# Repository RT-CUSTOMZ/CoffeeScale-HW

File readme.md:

# HX711 Board

* RATE Pin connected to GND -> 10 Hz mode
* X1 Pin connected to GND -> on-chip oscillator is activate

## InteractiveHtmlBom

[Link to interactive bom](https://htmlpreview.github.io/?https://raw.githubusercontent.com/RT-CUSTOMZ/CoffeeScale-HW/master/bom/ibom.html)

## Schematics

[Link to Schematic pdf](./coffee-scale.pdf )

## Messbrücke

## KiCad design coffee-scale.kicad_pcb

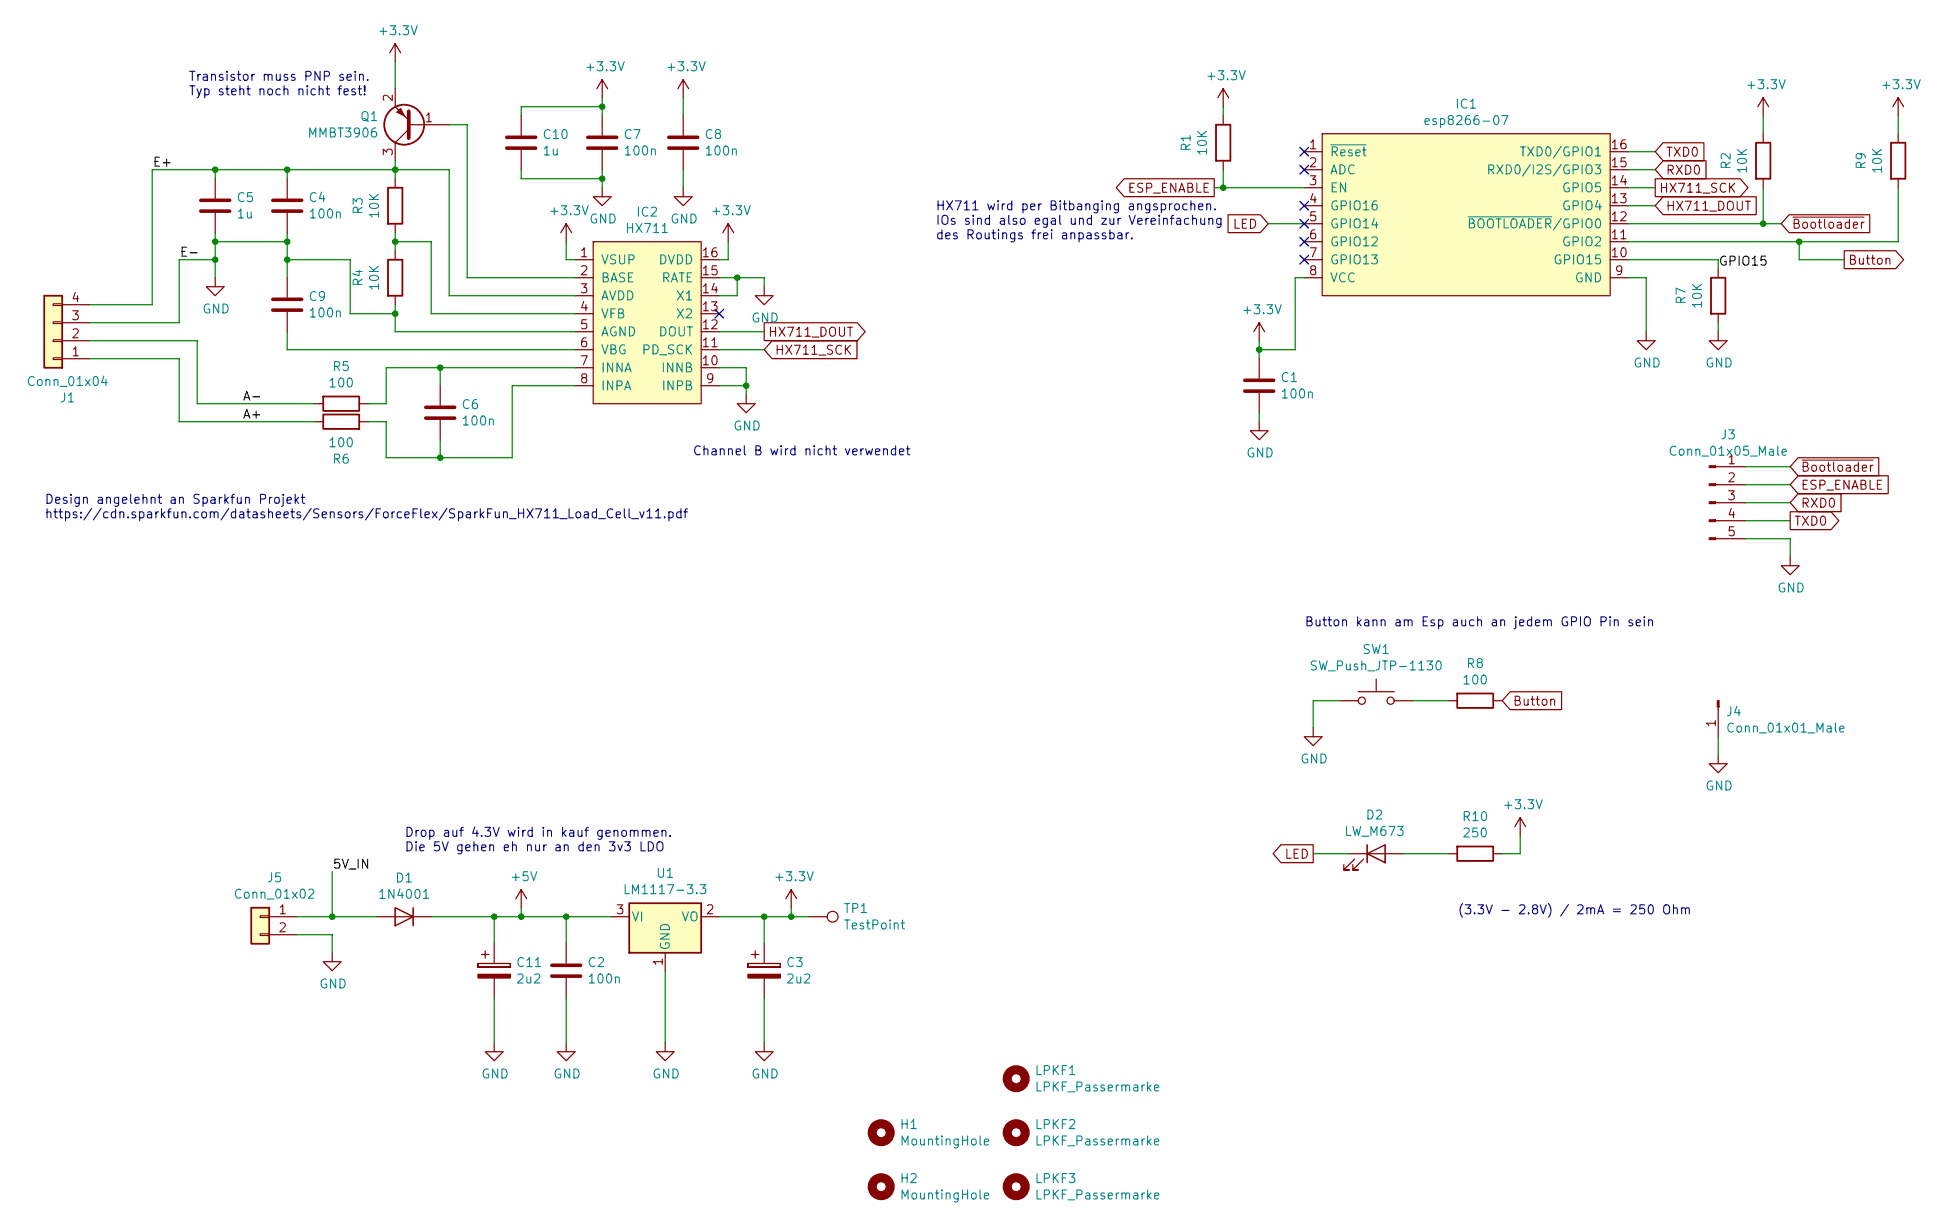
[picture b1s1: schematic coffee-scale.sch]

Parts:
C1, C2, C4, C6, C7, C8, C9: 100n; C_0805_2012Metric_Pad1.15x1.40mm_HandSolder
C3, C11: 2u2; CP_Elec_4x5.4
C5, C10: 1u; C_0805_2012Metric_Pad1.15x1.40mm_HandSolder
D1: 1N4001; D_MELF_Handsoldering
D2: LW_M673
H1, H2: MountingHole; MountingHole_5.5mm
IC1: esp8266-07; ESP-07_smd
IC2: HX711; SOP-16_4.4x10.4mm_P1.27mm
J1: Conn_01x04; PinHeader_1x04_P2.54mm_Horizontal
J3: Conn_01x05_Male; PinHeader_1x05_P2.54mm_Vertical
J4: Conn_01x01_Male; SolderWirePad_1x01_Drill1.2mm
J5: Conn_01x02; PinHeader_1x02_P2.54mm_Horizontal
LPKF1, LPKF2, LPKF3: LPKF_Passermarke; LPKF_Passermarke_Pad_D1.5mm
Q1: MMBT3906; SOT-23
R1, R2, R3, R4, R7, R9: 10K; R_0805_2012Metric_Pad1.15x1.40mm_HandSolder
R5, R6, R8: 100; R_0805_2012Metric_Pad1.15x1.40mm_HandSolder
R10: 250; R_0805_2012Metric_Pad1.15x1.40mm_HandSolder
SW1: SW_Push_JTP-1130; SW_SPST_JTP-1130
TP1: TestPoint; TestPoint_THTPad_D2.0mm_Drill1.0mm
U1: LM1117-3.3; SOT-223-3_TabPin2

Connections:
+3V3: C1.1, C3.1, C7.1, C8.1, C10.1, IC1.8 (VCC), IC2.1 (VSUP), IC2.16 (DVDD), Q1.2 (E), R1.1, R2.1, R9.1, R10.1, TP1.1, U1.2 (VO)
+5V: C2.1, C11.1, D1.1 (K), U1.3 (VI)
/5V_IN: D1.2 (A), J5.1
/A+: J1.1, R6.1
/A-: J1.2, R5.2
/E+: C4.1, C5.1, IC2.3 (AVDD), J1.4, Q1.3 (C), R3.1
/GPIO15: IC1.10 (GPIO15), R7.1
Button: IC1.11 (GPIO2), R8.1, R9.2
ESP_ENABLE: IC1.3 (EN), J3.2, R1.2
GND: C1.2, C2.2, C3.2, C4.2, C5.2, C7.2, C8.2, C9.1, C10.2, C11.2, IC1.9 (GND), IC2.5 (AGND), IC2.9 (INPB), IC2.10 (INNB), IC2.14 (X1), IC2.15 (RATE), J1.3, J3.5, J4.1, J5.2, R4.2, R7.2, SW1.1, U1.1 (GND)
HX711_DOUT: IC1.13 (GPIO4), IC2.12 (DOUT)
HX711_SCK: IC1.14 (GPIO5), IC2.11 (PD_SCK)
LED: D2.1 (K), IC1.5 (GPIO14)
unnamed: C6.1, IC2.7 (INNA), R5.1
unnamed: C6.2, IC2.8 (INPA), R6.2
unnamed: C9.2, IC2.6 (VBG)
unnamed: D2.2 (A), R10.2
unnamed: IC2.2 (BASE), Q1.1 (B)
unnamed: IC2.4 (VFB), R3.2, R4.1
unnamed: R8.2, SW1.2
RXD0: IC1.15 (RXD0/I2S/GPIO3), J3.3
TXD0: IC1.16 (TXD0/GPIO1), J3.4
~Bootloader: IC1.12 (~BOOTLOADER~/GPIO0), J3.1, R2.2

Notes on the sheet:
Transistor muss PNP sein. Typ steht noch nicht fest!
Channel B wird nicht verwendet
Design angelehnt an Sparkfun Projekt https://cdn.sparkfun.com/datasheets/Sensors/ForceFlex/SparkFun_HX711_Load_Cell_v11.pdf
HX711 wird per Bitbanging angsprochen. IOs sind also egal und zur Vereinfachung des Routings frei anpassbar.
Drop auf 4.3V wird in kauf genommen. Die 5V gehen eh nur an den 3v3 LDO
Button kann am Esp auch an jedem GPIO Pin sein
(3.3V - 2.8V) / 2mA = 250 Ohm

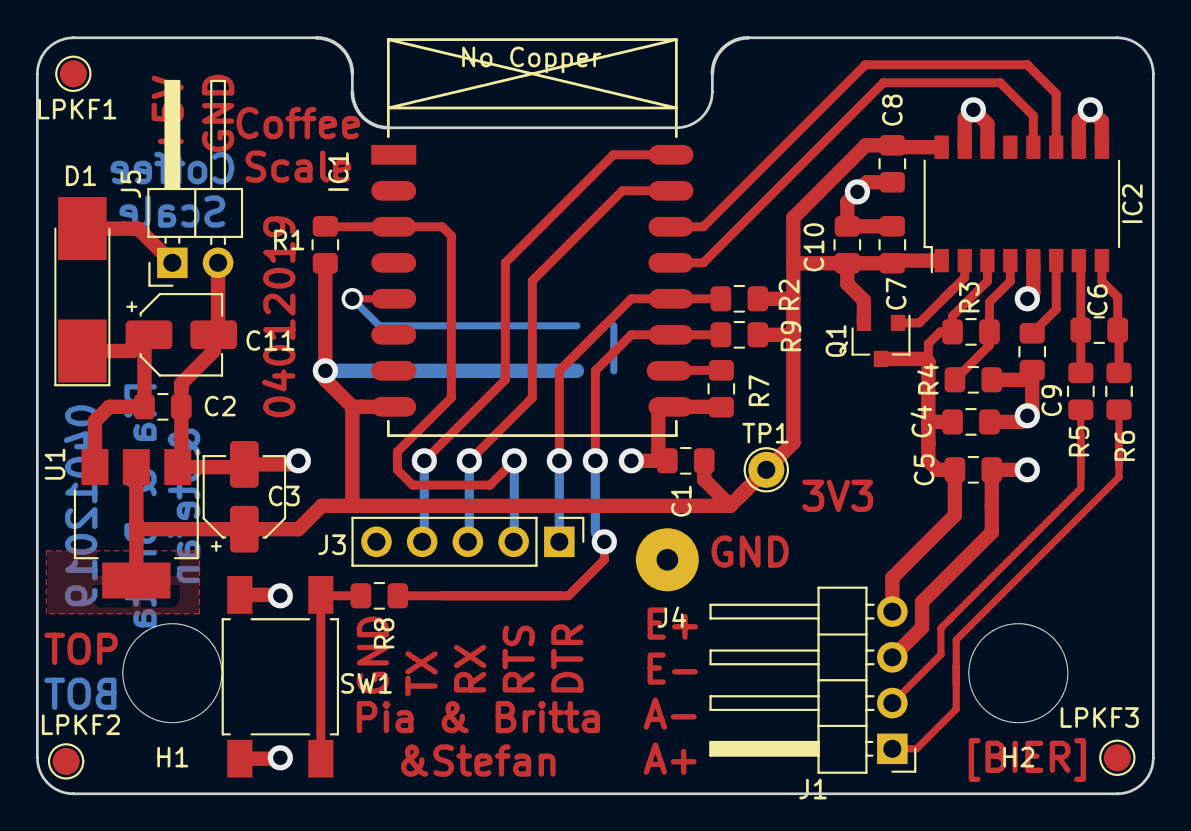
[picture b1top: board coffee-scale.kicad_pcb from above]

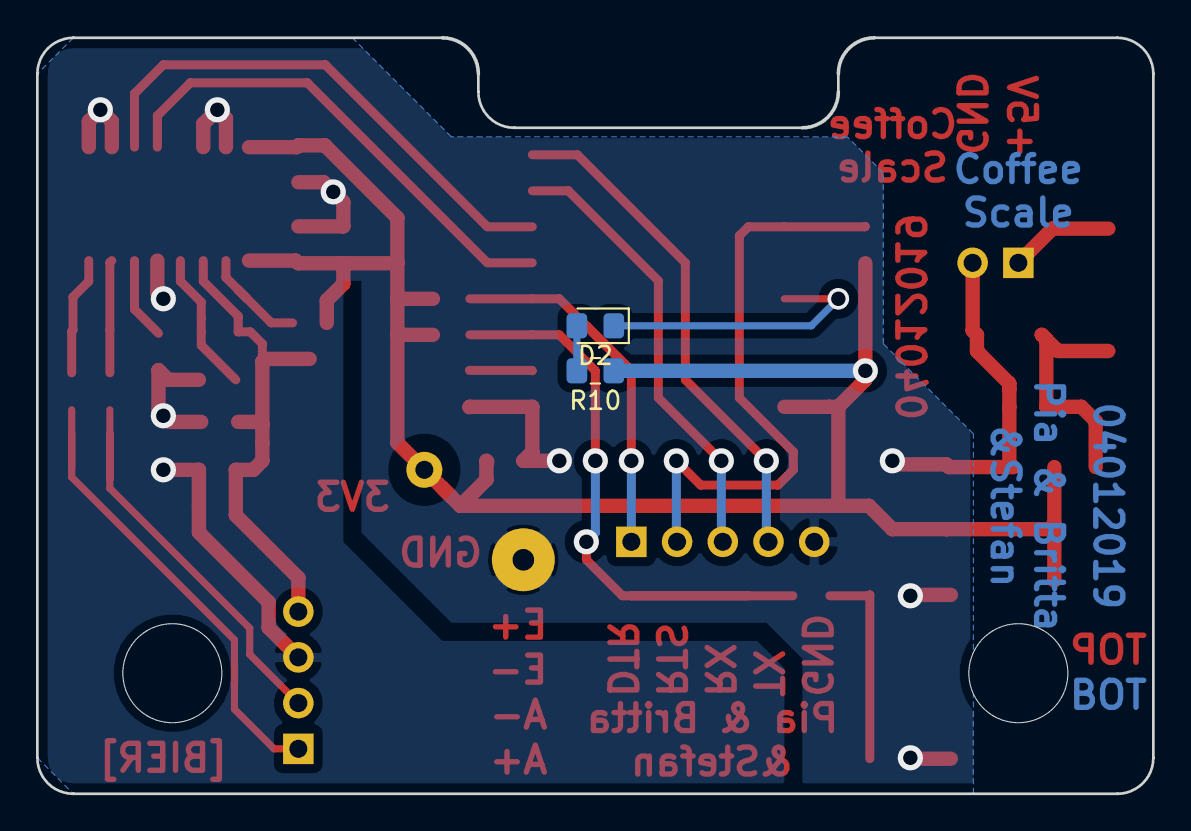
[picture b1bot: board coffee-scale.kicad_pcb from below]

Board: 2 copper layers, 62.0 x 42.0 mm, 38 parts (2 on the bottom side), 23 nets.

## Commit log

2019-01-05 next pcb version
    fix esp position
    add descriptions to copper
    fix hole positions
2019-01-24 add documentation to readme.md
2019-01-24 add link to pdf for readme.md
2019-01-24 fix typo
2019-01-24 add bridge picture
2019-02-21 add interactivehtmlbom
2019-02-21 Update readme.md
    add link to interactive html bom
